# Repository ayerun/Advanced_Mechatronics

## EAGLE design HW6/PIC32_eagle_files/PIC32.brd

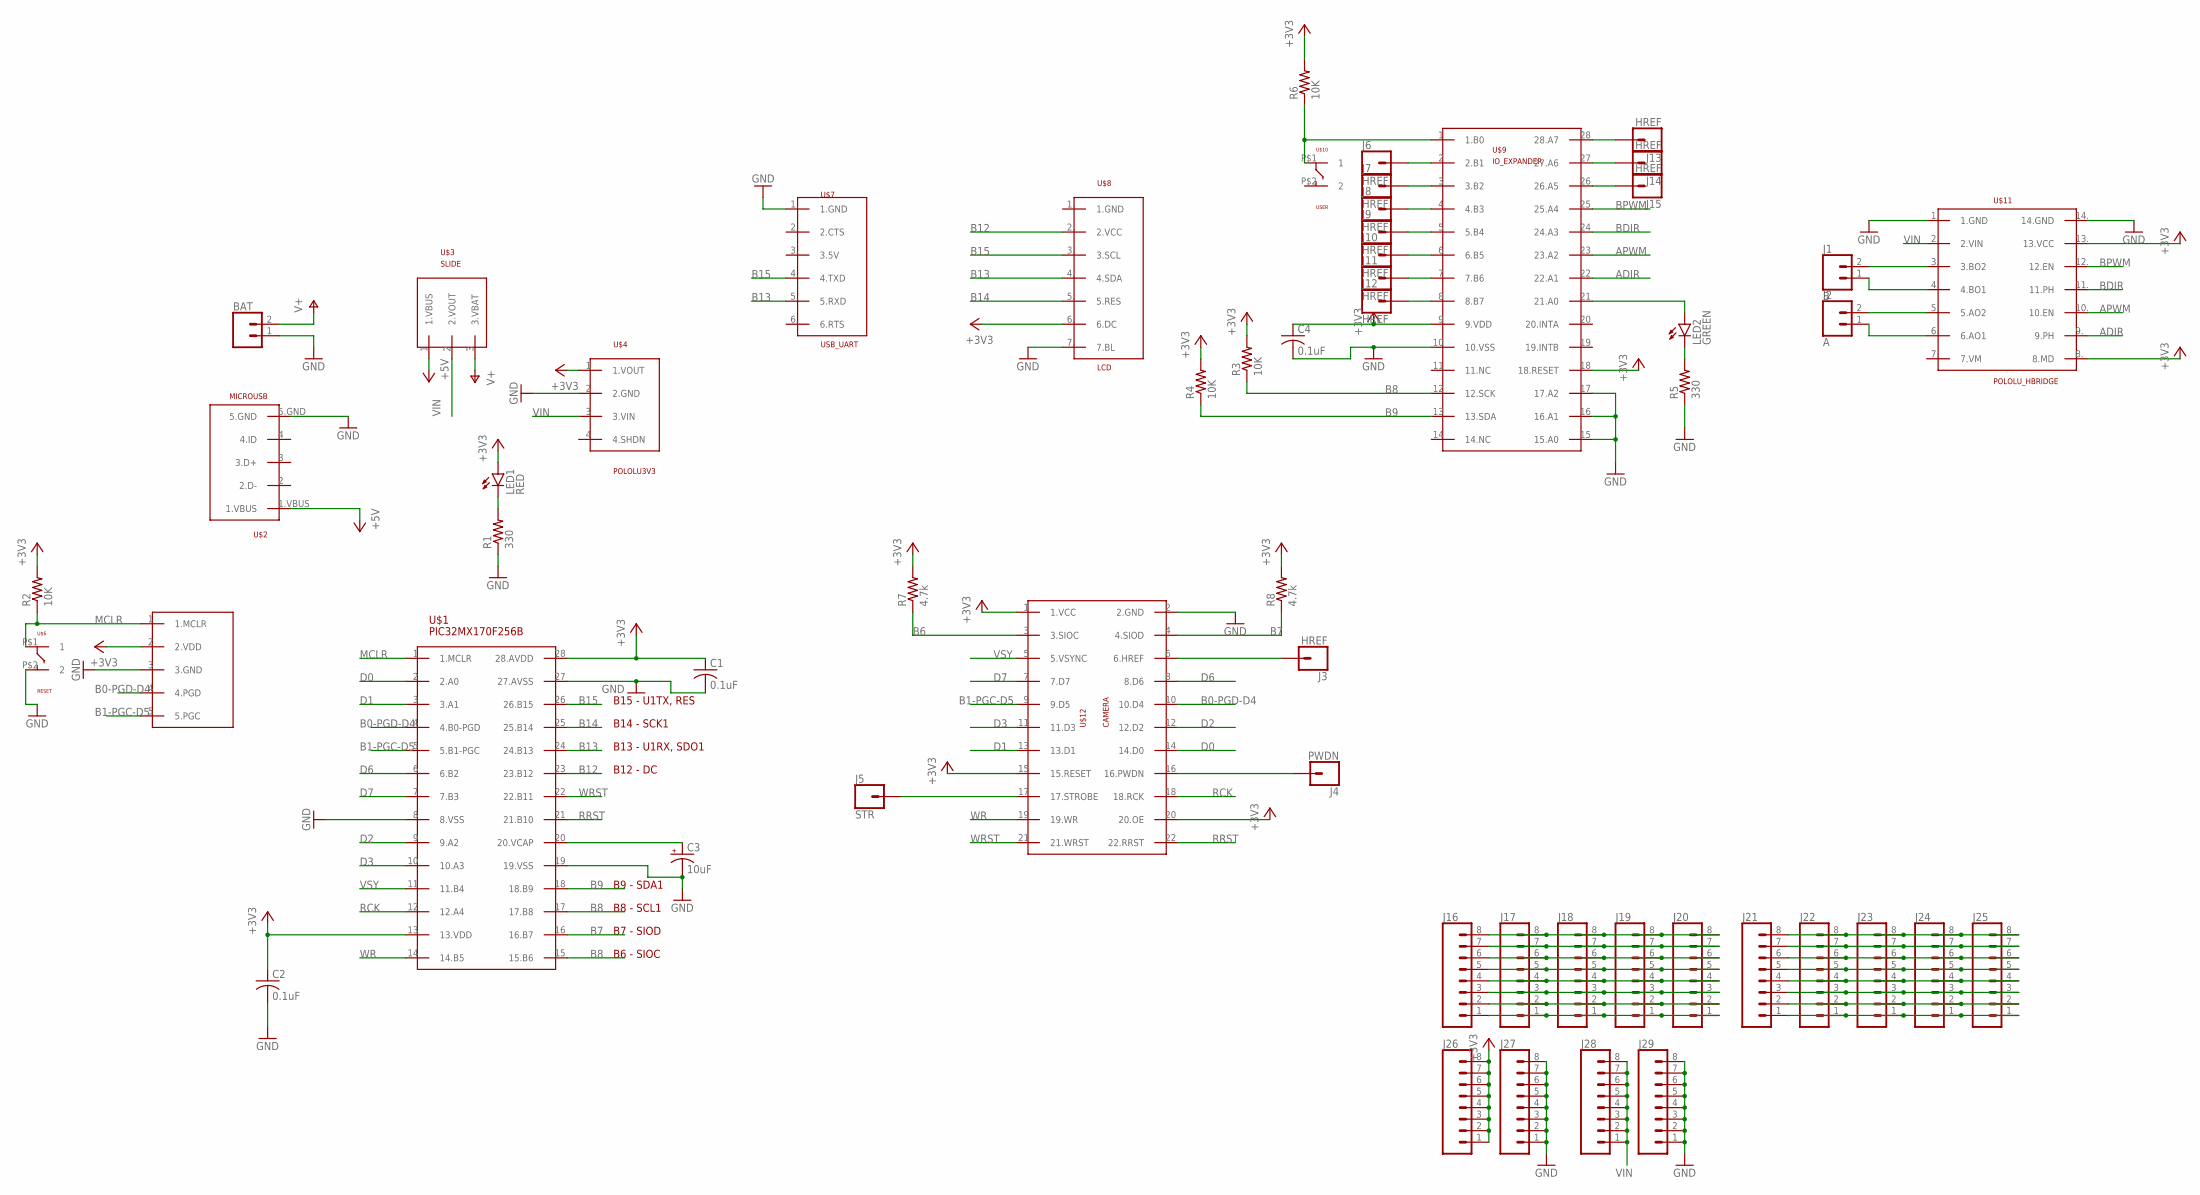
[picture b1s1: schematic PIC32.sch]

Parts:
BAT: CONN_02; 1X02
C1, C2, C4: 0.1uF; C025-025X050
C3: 10uF; B45181B
J1: B; 1X02
J2: A; 1X02
J3, J6, J7, J8, J9, J10, J11, J12, J13, J14, J15: HREF; 1X01
J4: PWDN; 1X01
J5: STR; 1X01
J16, J17, J18, J19, J20, J21, J22, J23, J24, J25, J26, J27, J28, J29: CONN_08"; 1X08
LED1: RED; LED3MM
LED2: GREEN; LED3MM
R1, R5: 330; 0207/10
R2, R3, R4, R6: 10K; 0207/10
R7, R8: 4.7k; 0207/10
U$1: PIC32MX170F256B; DIL28-3
U$2: MICROUSB
U$3: SLIDE
U$4: POLOLU3V3
U$5: SNAP
U$6: RESET; PUSH
U$7: USB_UART
U$8: LCD
U$9: IO_EXPANDER; DIL28-3
U$10: USER; PUSH
U$11: POLOLU_HBRIDGE
U$12: CAMERA

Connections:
+3V3: C1.1, C2.1, C4.1, J26.1, J26.2, J26.3, J26.4, J26.5, J26.6, J26.7, J26.8, LED1.A, R2.2, R3.2, R4.2, R6.2, R7.2, R8.2, U$1.13 (13.VDD), U$1.28 (28.AVDD), U$4.1 (1.VOUT), U$5.2 (2.VDD), U$8.6. (6.DC), U$9.9 (9.VDD), U$9.18 (18.RESET), U$11.8. (8.MD), U$11.13. (13.VCC), U$12.1 (1.VCC), U$12.15 (15.RESET), U$12.20 (20.OE)
+5V: U$2.1.VBUS, U$3.1 (1.VBUS)
ADIR: U$9.22 (22.A1), U$11.9. (9.PH)
APWM: U$9.23 (23.A2), U$11.10. (10.EN)
B0-PGD-D4: U$1.4 (4.B0-PGD), U$5.4 (4.PGD), U$12.10 (10.D4)
B1-PGC-D5: U$1.5 (5.B1-PGC), U$5.5 (5.PGC), U$12.9 (9.D5)
B6: R7.1, U$12.3 (3.SIOC)
B7: R8.1, U$1.16 (16.B7), U$12.4 (4.SIOD)
B8: R3.1, U$1.15 (15.B6), U$1.17 (17.B8), U$9.12 (12.SCK)
B9: R4.1, U$1.18 (18.B9), U$9.13 (13.SDA)
B12: U$1.23 (23.B12), U$8.2. (2.VCC)
B13: U$1.24 (24.B13), U$7.5. (5.RXD), U$8.4. (4.SDA)
B14: U$1.25 (25.B14), U$8.5. (5.RES)
B15: U$1.26 (26.B15), U$7.4. (4.TXD), U$8.3. (3.SCL)
BDIR: U$9.24 (24.A3), U$11.11. (11.PH)
BPWM: U$9.25 (25.A4), U$11.12. (12.EN)
D0: U$1.2 (2.A0), U$12.14 (14.D0)
D1: U$1.3 (3.A1), U$12.13 (13.D1)
D2: U$1.9 (9.A2), U$12.12 (12.D2)
D3: U$1.10 (10.A3), U$12.11 (11.D3)
D6: U$1.6 (6.B2), U$12.8 (8.D6)
D7: U$1.7 (7.B3), U$12.7 (7.D7)
GND: BAT.1, C1.2, C2.2, C3.-, C4.2, J27.1, J27.2, J27.3, J27.4, J27.5, J27.6, J27.7, J27.8, J29.1, J29.2, J29.3, J29.4, J29.5, J29.6, J29.7, J29.8, R1.1, R5.1, U$1.8 (8.VSS), U$1.19 (19.VSS), U$1.27 (27.AVSS), U$2.5.GND, U$4.2 (2.GND), U$5.3 (3.GND), U$6.P$2 (2), U$7.1. (1.GND), U$8.7. (7.BL), U$9.10 (10.VSS), U$9.15 (15.A0), U$9.16 (16.A1), U$9.17 (17.A2), U$11.1. (1.GND), U$11.14. (14.GND), U$12.2 (2.GND)
MCLR: R2.1, U$1.1 (1.MCLR), U$5.1 (1.MCLR), U$6.P$1 (1)
unnamed: LED1.K (C), R1.2
unnamed: C3.+, U$1.20 (20.VCAP)
unnamed: R6.1, U$9.1 (1.B0), U$10.P$1 (1)
unnamed: J1.2, U$11.3. (3.BO2)
unnamed: LED2.A, U$9.21 (21.A0)
unnamed: LED2.K (C), R5.2
unnamed: J1.1, U$11.4. (4.BO1)
unnamed: J2.2, U$11.5. (5.AO2)
unnamed: J2.1, U$11.6. (6.AO1)
unnamed: J5.1, U$12.17 (17.STROBE)
unnamed: J4.1, U$12.16 (16.PWDN)
unnamed: J3.1, U$12.6 (6.HREF)
unnamed: J6.1, U$9.2 (2.B1)
unnamed: J7.1, U$9.3 (3.B2)
unnamed: J8.1, U$9.4 (4.B3)
unnamed: J9.1, U$9.5 (5.B4)
unnamed: J10.1, U$9.6 (6.B5)
unnamed: J11.1, U$9.7 (7.B6)
unnamed: J12.1, U$9.8 (8.B7)
unnamed: J15.1, U$9.26 (26.A5)
unnamed: J14.1, U$9.27 (27.A6)
unnamed: J13.1, U$9.28 (28.A7)
unnamed: J16.8, J17.8, J18.8, J19.8, J20.8
unnamed: J16.7, J17.7, J18.7, J19.7, J20.7
unnamed: J16.6, J17.6, J18.6, J19.6, J20.6
unnamed: J16.5, J17.5, J18.5, J19.5, J20.5
unnamed: J16.4, J17.4, J18.4, J19.4, J20.4
unnamed: J16.3, J17.3, J18.3, J19.3, J20.3
unnamed: J16.2, J17.2, J18.2, J19.2, J20.2
unnamed: J16.1, J17.1, J18.1, J19.1, J20.1
unnamed: J21.8, J22.8, J23.8, J24.8, J25.8
unnamed: J21.7, J22.7, J23.7, J24.7, J25.7
unnamed: J21.6, J22.6, J23.6, J24.6, J25.6
unnamed: J21.5, J22.5, J23.5, J24.5, J25.5
unnamed: J21.4, J22.4, J23.4, J24.4, J25.4
unnamed: J21.3, J22.3, J23.3, J24.3, J25.3
unnamed: J21.2, J22.2, J23.2, J24.2, J25.2
unnamed: J21.1, J22.1, J23.1, J24.1, J25.1
RCK: U$1.12 (12.A4), U$12.18 (18.RCK)
RRST: U$1.21 (21.B10), U$12.22 (22.RRST)
V+: BAT.2, U$3.3 (3.VBAT)
VIN: J28.1, J28.2, J28.3, J28.4, J28.5, J28.6, J28.7, J28.8, U$3.2 (2.VOUT), U$4.3 (3.VIN), U$11.2. (2.VIN)
VSY: U$1.11 (11.B4), U$12.5 (5.VSYNC)
WR: U$1.14 (14.B5), U$12.19 (19.WR)
WRST: U$1.22 (22.B11), U$12.21 (21.WRST)

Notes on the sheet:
B15 - U1TX, RES
B13 - U1RX, SDO1
B14 - SCK1
B12 - DC
B9 - SDA1
B8 - SCL1
B7 - SIOD
B6 - SIOC

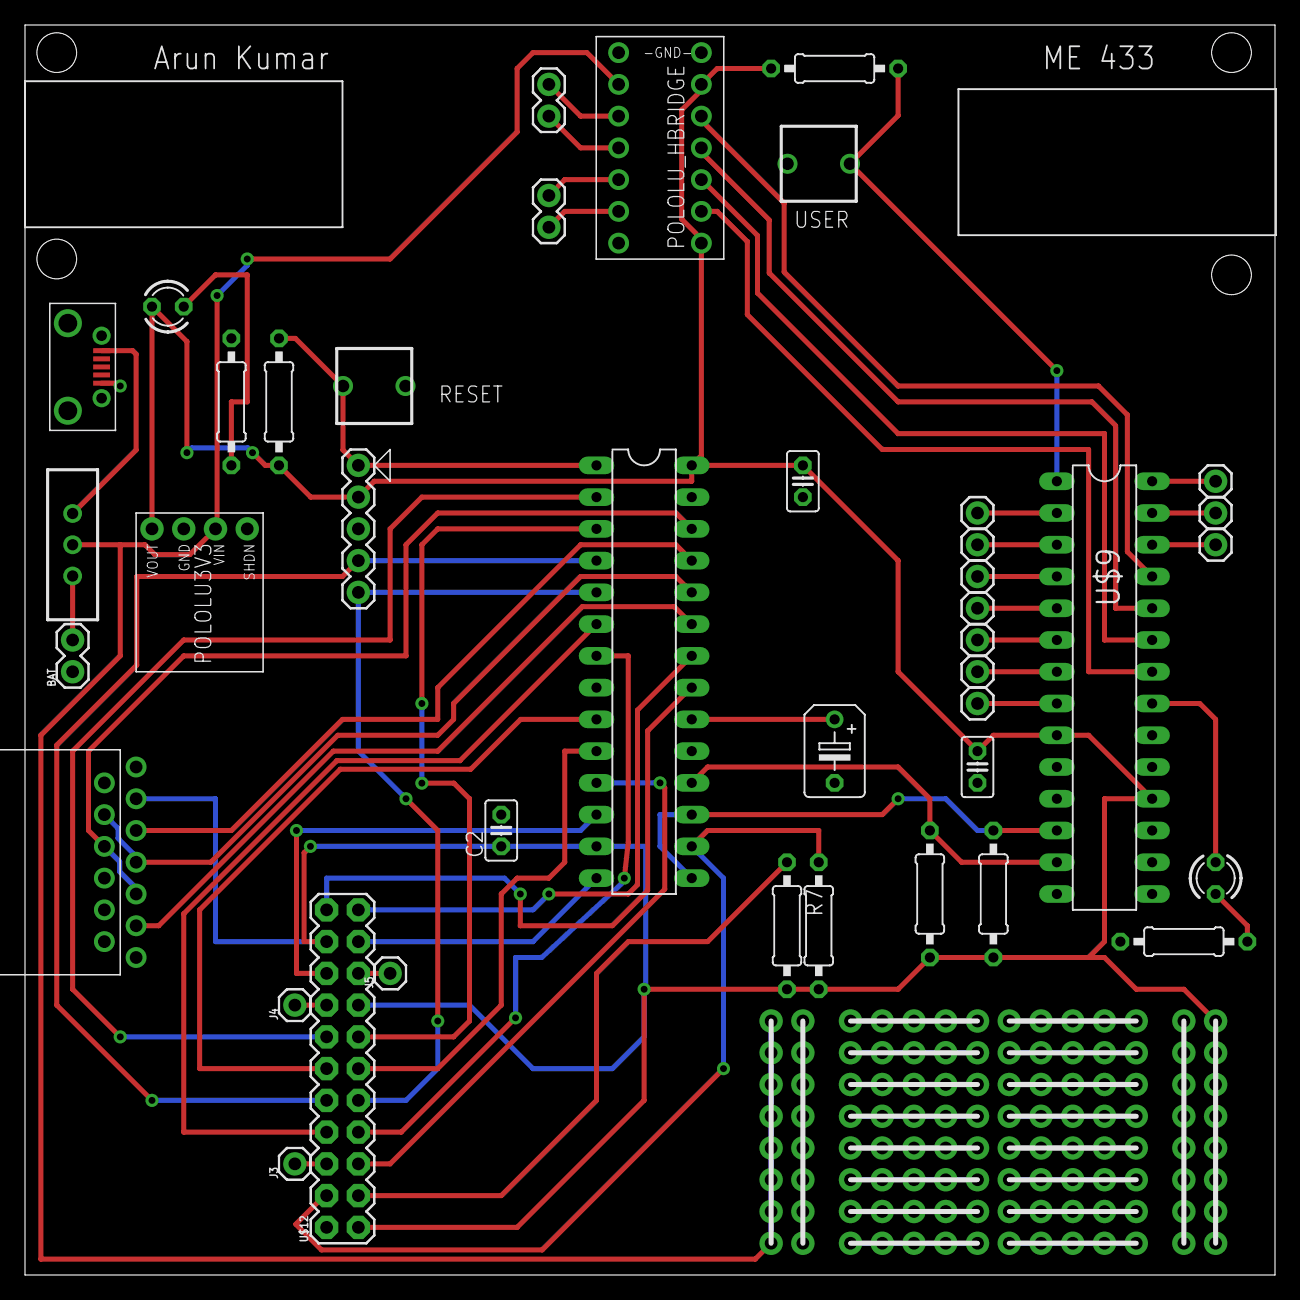
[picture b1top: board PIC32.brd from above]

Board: 2 copper layers, 100.0 x 100.0 mm, 56 parts (1 on the bottom side), 69 nets.

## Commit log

2021-04-03 completed 4 and started 5 in HW2
2021-04-03 finished 5
2021-04-03 added images of plots
2021-04-03 finished question 6 6.py is IIR 6_2.py is lowpass then IIR
2021-04-04 added images for 6 finished 6
2021-04-05 finished 7 and created images
2021-04-05 removed 6_2
2021-04-08 finished hw3
2021-04-11 finished hw4
2021-04-11 added demo video
2021-04-21 finished homework 5 UART communication
2021-04-30 finished homework 7
2021-05-25 finished hw6
2021-05-28 finished HW8
2021-05-28 fixed i2c initialization error
2021-05-29 finished HW10
2021-05-29 finished HW9
2021-06-08 finished hw11
2021-06-10 finished HW16
